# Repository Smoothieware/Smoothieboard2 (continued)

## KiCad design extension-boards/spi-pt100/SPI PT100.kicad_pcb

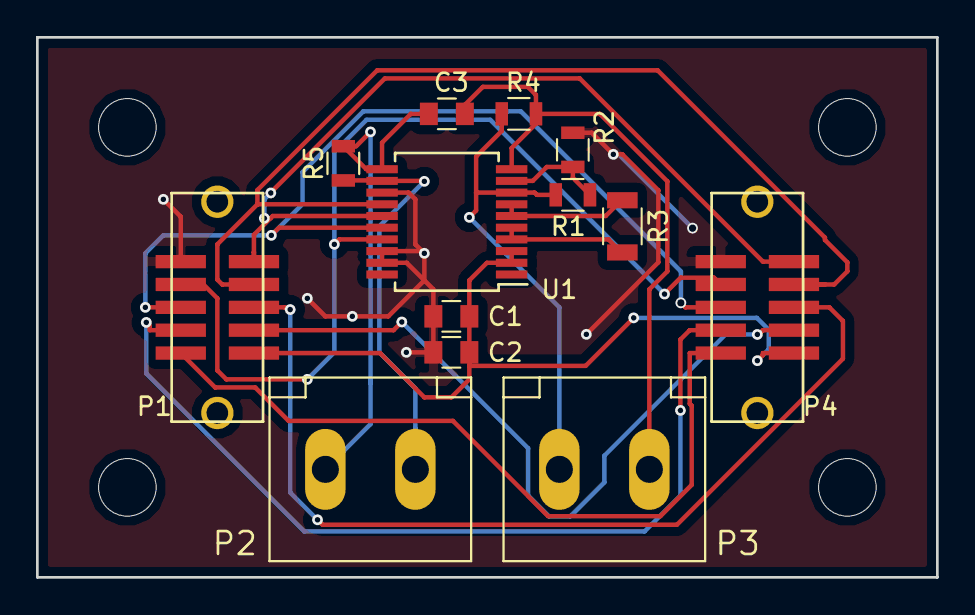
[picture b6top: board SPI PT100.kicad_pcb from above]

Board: 2 copper layers, 50.0 x 30.0 mm, 17 parts (0 on the bottom side), 17 nets.

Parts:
C1, C2: 0.1u; C_0805
C3: 10n; C_0805
M1, M2, M3, M4: MH_M3; MountingHole_3.2mm_M3
P1, P4: Smoothie-teer-S; SHF-105-01-L-D-SM-LC
P2, P3: Conn_1x02; Weidmuller_1715250000
R1: NM; R_0805
R2, R4, R5: 0; R_0805
R3: 400; R_1206
U1: MAX31865_SSOP20; SSOP-20_5.3x7.2mm_Pitch0.65mm

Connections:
GND: C1.2, C2.2, P1.10, P4.10, R2.1, U1.13, U1.18, U1.19
unnamed: C1.1, C2.1, P1.1, P4.1, U1.2, U1.3
unnamed: C3.1, P3.2, R4.2, U1.10
unnamed: C3.2, P2.1, R5.2, U1.11
unnamed: P1.2, P4.2
unnamed: P1.3, P4.3
unnamed: P1.4, P4.4
unnamed: P1.5, P4.5
unnamed: P1.6, P4.6, U1.16
unnamed: P1.7, P4.7, U1.14
unnamed: P1.8, P4.8, U1.17
unnamed: P1.9, P4.9, U1.15
unnamed: P2.2, R5.1, U1.12
unnamed: P3.1, R1.1, R4.1, U1.8
unnamed: R1.2, R2.2, U1.9
unnamed: R3.1, U1.4, U1.5
unnamed: R3.2, U1.6, U1.7

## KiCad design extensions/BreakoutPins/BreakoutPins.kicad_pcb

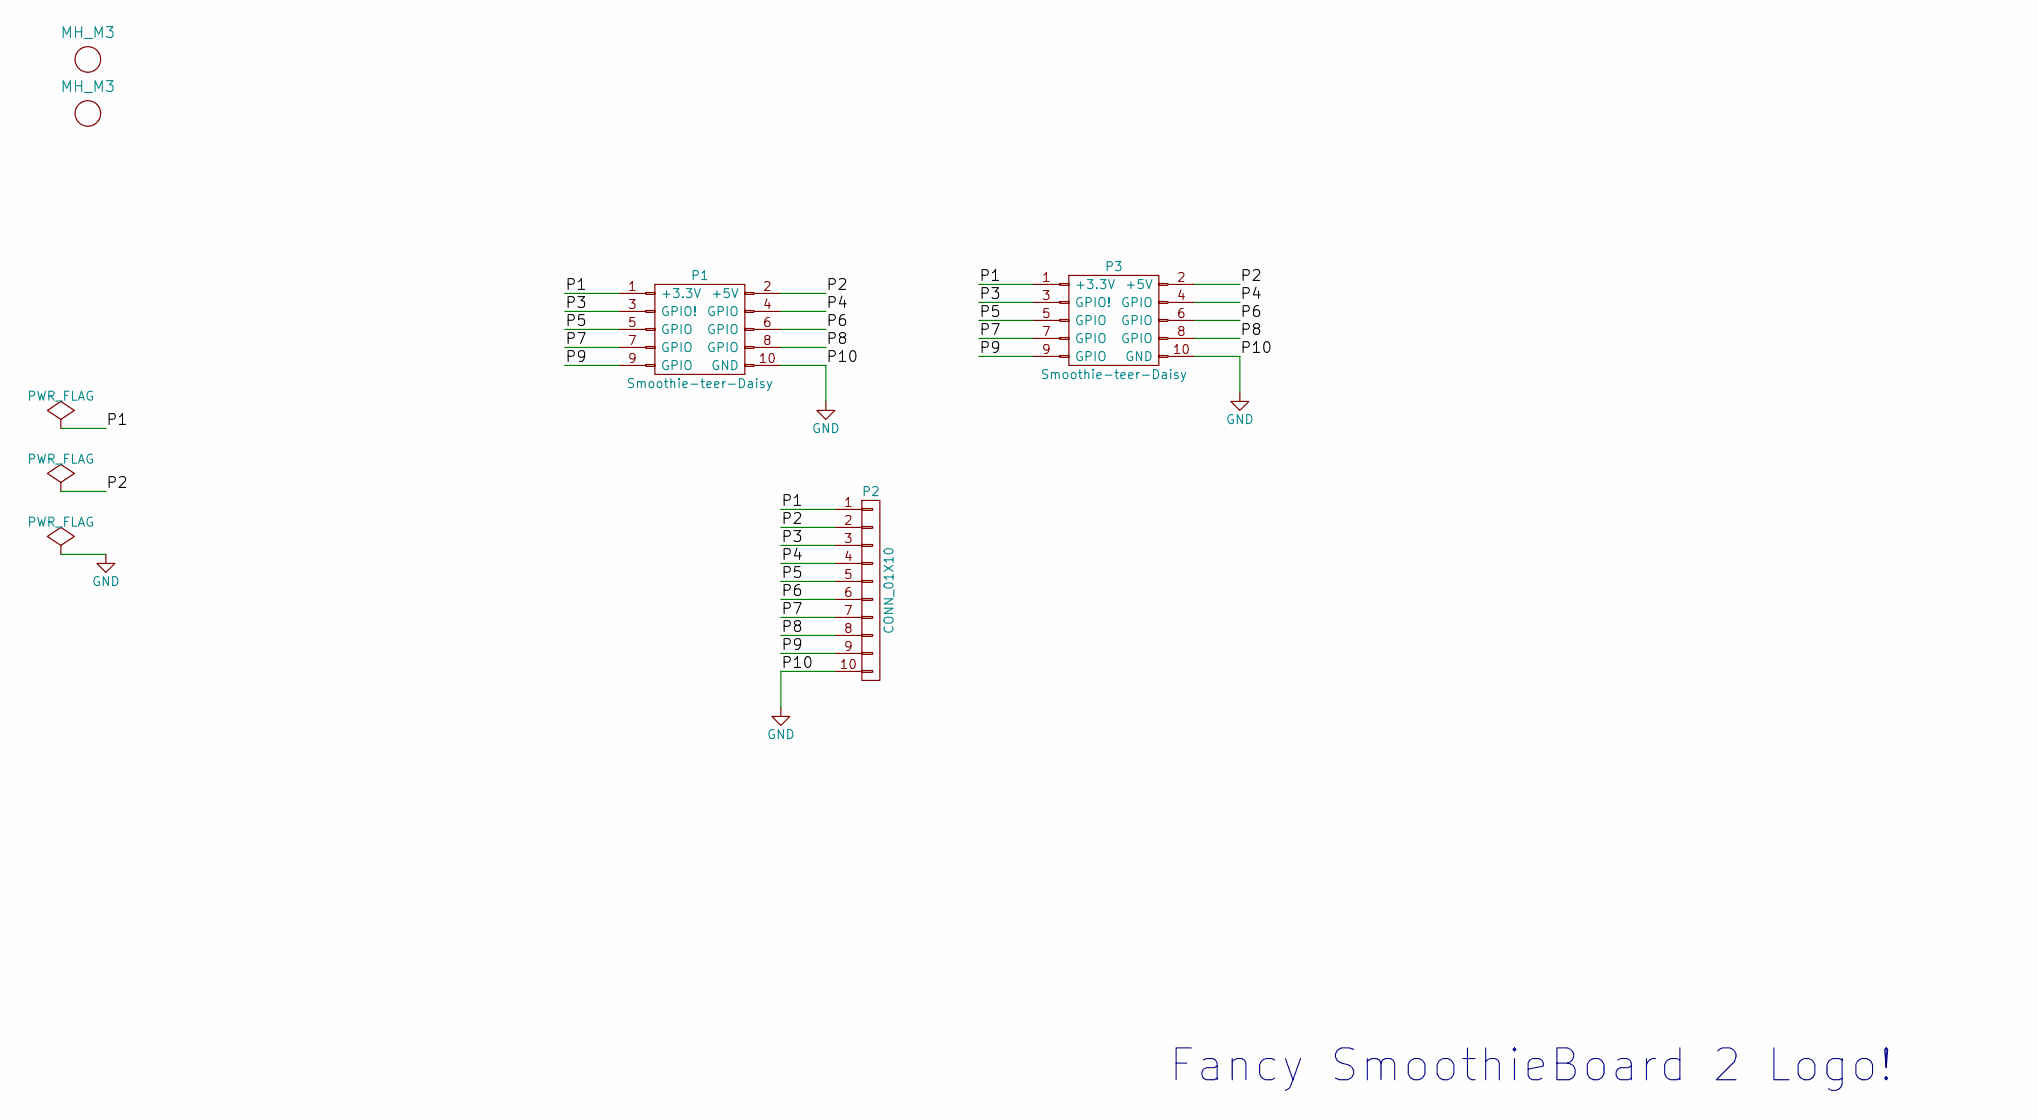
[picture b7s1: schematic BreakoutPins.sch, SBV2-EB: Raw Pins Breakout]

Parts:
M1, M2: MH_M3; M3_Mounting_Hole; Digikey Part No. ND
P1, P3: Smoothie-teer-Daisy; 20021521-00010T1LF
P2: CONN_01X10; Socket_Strip_Straight_1x10

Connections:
/P1: P1.1 (+3.3V), P2.1, P3.1 (+3.3V)
/P2: P1.2 (+5V), P2.2, P3.2 (+5V)
/P3: P1.3 (GPIO!), P2.3, P3.3 (GPIO!)
/P4: P1.4 (GPIO), P2.4, P3.4 (GPIO)
/P5: P1.5 (GPIO), P2.5, P3.5 (GPIO)
/P6: P1.6 (GPIO), P2.6, P3.6 (GPIO)
/P7: P1.7 (GPIO), P2.7, P3.7 (GPIO)
/P8: P1.8 (GPIO), P2.8, P3.8 (GPIO)
/P9: P1.9 (GPIO), P2.9, P3.9 (GPIO)
GND: P1.10 (GND), P2.10, P3.10 (GND)

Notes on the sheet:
Fancy SmoothieBoard 2 Logo!

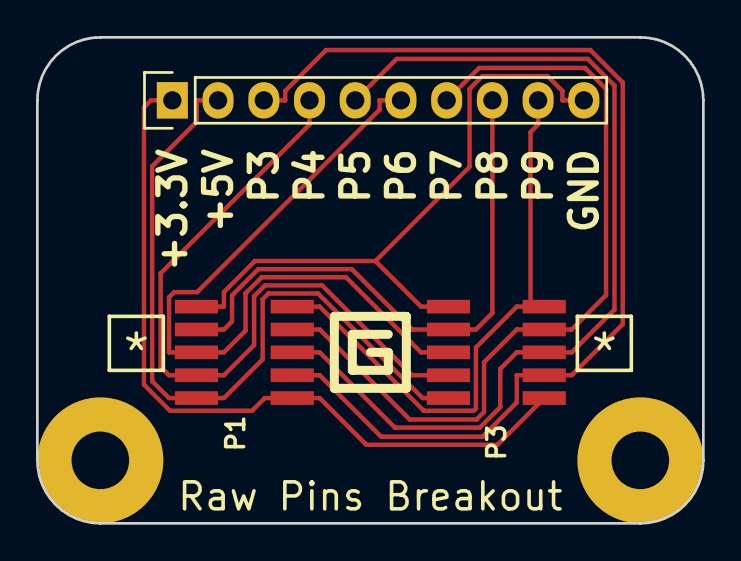
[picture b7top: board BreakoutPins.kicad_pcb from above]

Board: 2 copper layers, 37.0 x 27.0 mm, 5 parts (0 on the bottom side), 10 nets.

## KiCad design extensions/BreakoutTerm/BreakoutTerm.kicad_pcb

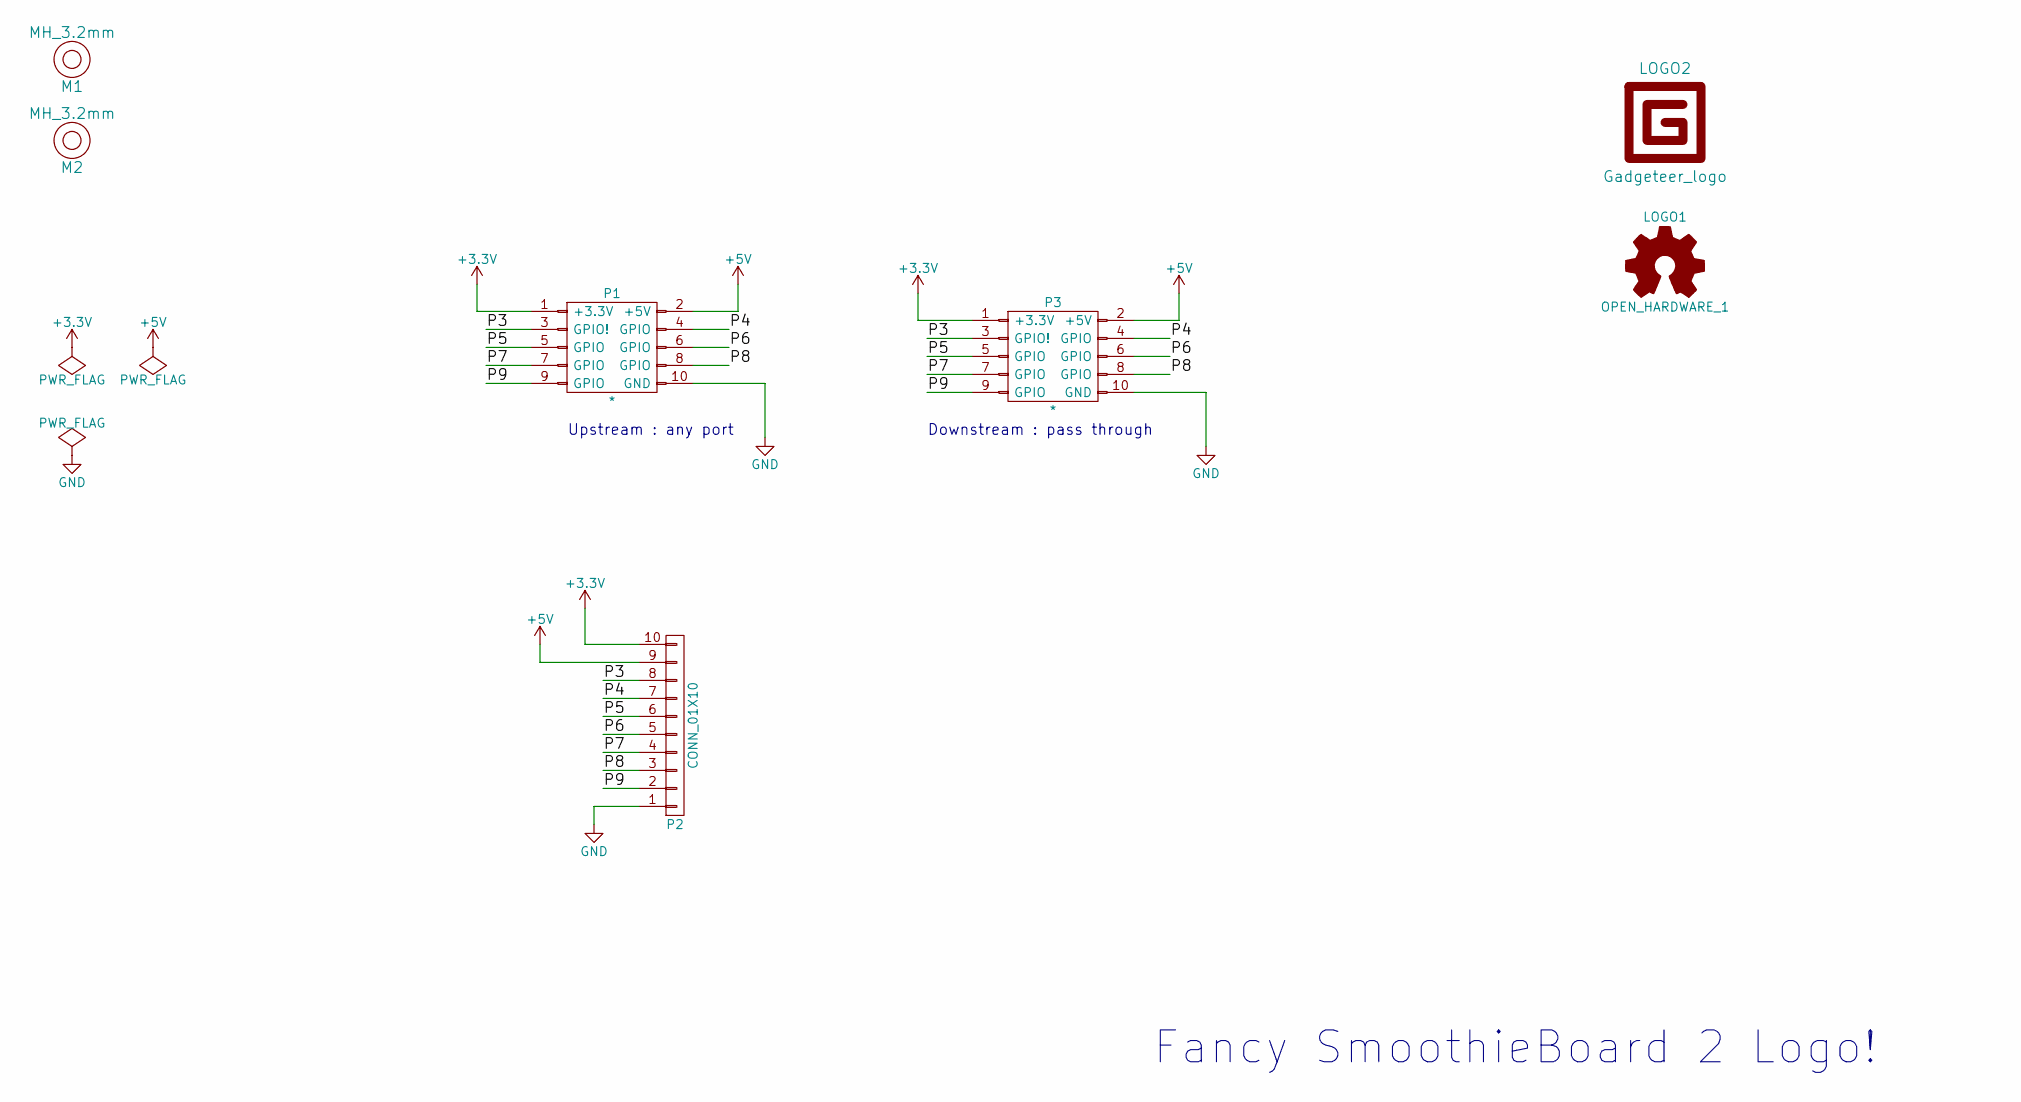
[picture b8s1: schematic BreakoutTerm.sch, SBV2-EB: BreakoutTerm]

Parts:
LOGO1: OPEN_HARDWARE_1; Logo_silk_OSHW_12x13mm
LOGO2: Gadgeteer_logo
M1, M2: MH_3.2mm; M3_Mounting_Hole
P1, P3: *; ESHF-105-01-L-D-SM
P2: CONN_01X10; TerminalBlock_Pheonix_PT-3.5mm_10pol

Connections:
+3V3: P1.1 (+3.3V), P2.10, P3.1 (+3.3V)
+5V: P1.2 (+5V), P2.9, P3.2 (+5V)
/P3: P1.3 (GPIO!), P2.8, P3.3 (GPIO!)
/P4: P1.4 (GPIO), P2.7, P3.4 (GPIO)
/P5: P1.5 (GPIO), P2.6, P3.5 (GPIO)
/P6: P1.6 (GPIO), P2.5, P3.6 (GPIO)
/P7: P1.7 (GPIO), P2.4, P3.7 (GPIO)
/P8: P1.8 (GPIO), P2.3, P3.8 (GPIO)
/P9: P1.9 (GPIO), P2.2, P3.9 (GPIO)
GND: P1.10 (GND), P2.1, P3.10 (GND)

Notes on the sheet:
Fancy SmoothieBoard 2 Logo!
Upstream : any port
Downstream : pass through

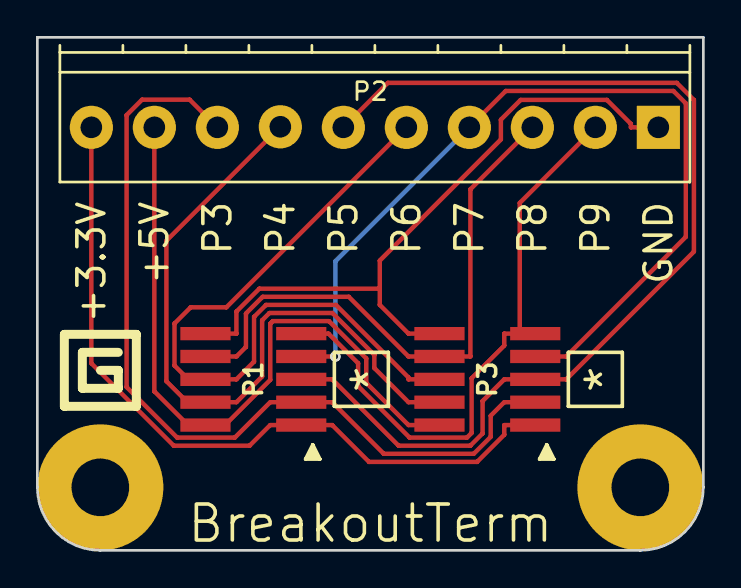
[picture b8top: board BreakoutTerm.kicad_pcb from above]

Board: 2 copper layers, 37.0 x 28.5 mm, 7 parts (1 on the bottom side), 10 nets.
